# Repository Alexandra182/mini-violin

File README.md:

# mini-violin
A mini PCB violin based on an ATTiny85 microcontroller ♫

Documentation: https://www.hackster.io/alexandracovor/attiny85-mini-pcb-violin-d728e5

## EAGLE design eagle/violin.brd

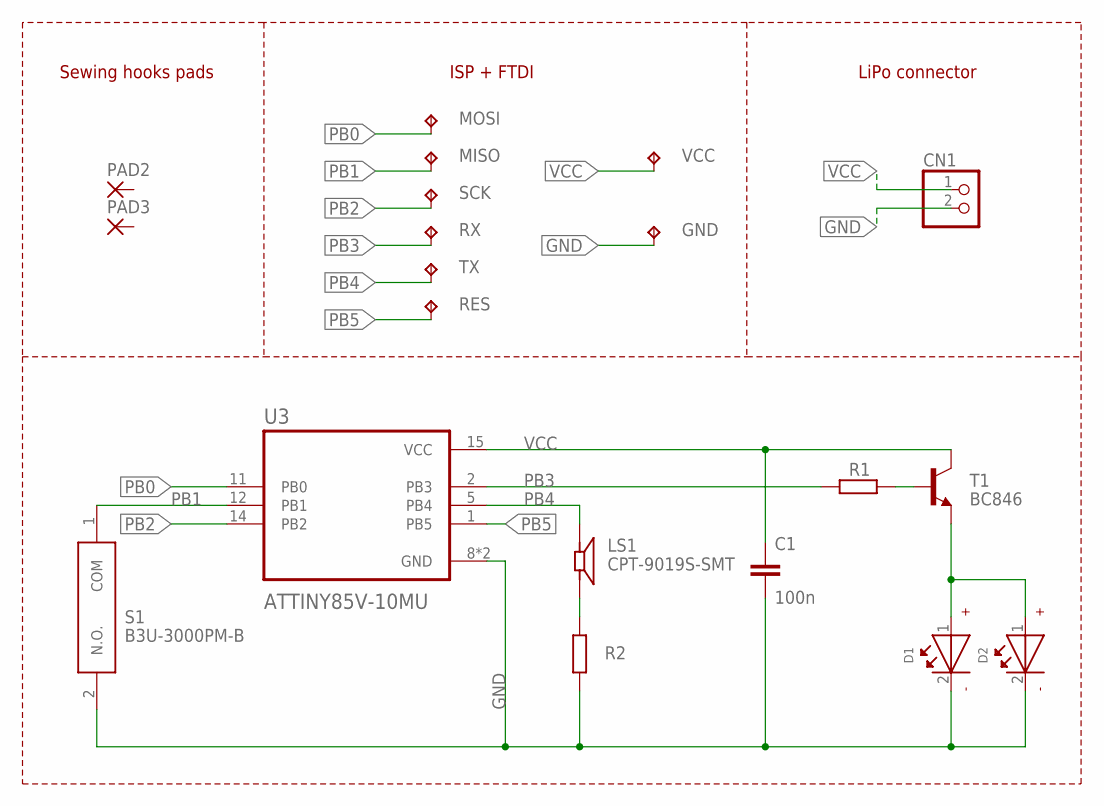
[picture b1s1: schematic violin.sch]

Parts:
C1: 100n; C0603
CN1: JST_2PIN; JSTPH2
D1, D2: WL-SMSW155124YS73200-Y; WL-SMSW_1204
GND: TPTP11SQ; TP11SQ
LS1: CPT-9019S-SMT; CUI_CPT-9019S-SMT
MISO: TPTP11SQ; TP11SQ
MOSI: TPTP11SQ; TP11SQ
PAD2: SMD5; SMD2,54-5,08
PAD3: SMD2; SMD1,27-2,54
R1, R2: R-EU_R0603; R0603
RES: TPTP11SQ; TP11SQ
RX: TPTP11SQ; TP11SQ
S1: B3U-3000PM-B; B3U3000PMB
SCK: TPTP11SQ; TP11SQ
T1: BC846; SOT23
TX: TPTP11SQ; TP11SQ
U3: ATTINY85V-10MU; QFN50P400X400X80-21N
VCC: TPTP11SQ; TP11SQ

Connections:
GND: C1.2, CN1.2, D1.2 (-), D2.2 (-), GND.TP, R2.1, S1.2 (N.O.), U3.8 (GND), U3.21 (GND)
unnamed: LS1.2, R2.2
unnamed: D1.1 (+), D2.1 (+), T1.2 (E)
unnamed: R1.2, T1.1 (B)
PB0: MOSI.TP, U3.11 (PB0)
PB1: MISO.TP, S1.1 (COM), U3.12 (PB1)
PB2: SCK.TP, U3.14 (PB2)
PB3: R1.1, RX.TP, U3.2 (PB3)
PB4: LS1.1, TX.TP, U3.5 (PB4)
PB5: RES.TP, U3.1 (PB5)
VCC: C1.1, CN1.1, T1.3 (C), U3.15 (VCC), VCC.TP

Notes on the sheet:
Sewing hooks pads
ISP + FTDI
LiPo connector

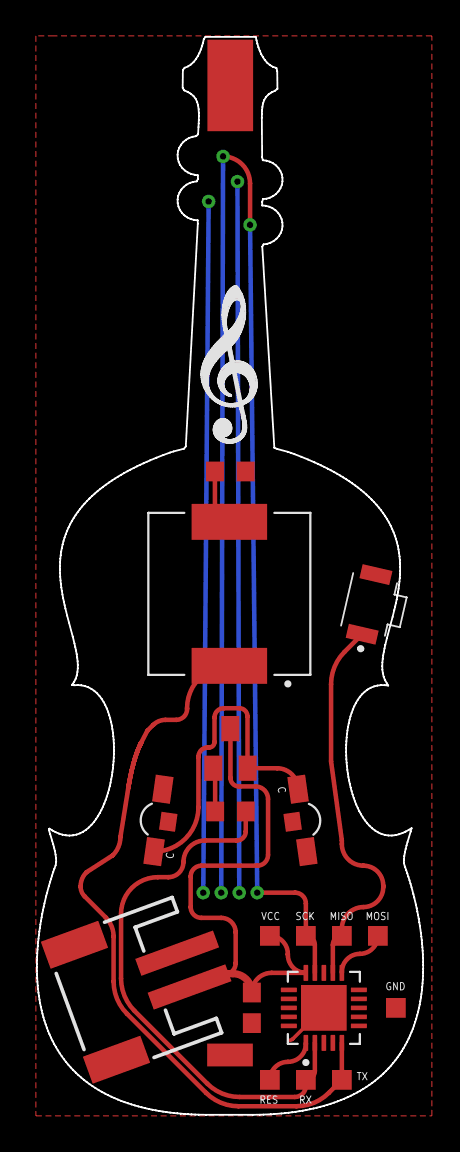
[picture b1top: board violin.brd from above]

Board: 2 copper layers, 21.5 x 59.9 mm, 20 parts (0 on the bottom side), 11 nets.

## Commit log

2020-10-10 Create LICENSE
2020-10-11 arduino code
2020-10-16 eagle files

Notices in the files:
parts and their libraries:
microbuilder: This work is placed in the public domain, and may be freely used for commercial and non-commercial work with the following conditions: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
